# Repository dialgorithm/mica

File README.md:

# mica

**mica** is a compact wireless FPV drone built around an **XIAO ESP32-S3**, with a custom-designed flight controller and a custom 3D-printed frame. The project focuses on building a lightweight, self-contained drone platform with **ExpressLRS (ELRS)** control, custom electronics, and a mechanical design tailored specifically to the hardware.

it features:

- XIAO ESP32-S3 as the main flight controller
- Custom-designed flight controller PCB
- ExpressLRS (ELRS) for wireless control
- Custom 3D-printed frame

## design

mica is designed around keeping the electronics and mechanical structure compact while still leaving enough space for the components required for flight.

the flight controller is built around the XIAO ESP32-S3, with the supporting electronics integrated onto a custom PCB. the frame was designed specifically around the PCB and drone hardware rather than using an off-the-shelf frame.

the 3d-printed structure keeps the drone lightweight while providing mounting points for the electronics and other components. the overall layout is kept symmetrical to help maintain the center of gravity and make the drone predictable during flight.

## Schematics + PCB

Designed using KiCad.

| Schematic                          | PCB                    |
| ---------------------------------- | ---------------------- |
|  |  |

## CAD

final 3d mockup of the drone frame.

|                                   |                                     |
| --------------------------------- | ----------------------------------- |
|  |  |

the frame is 3d printable and was designed specifically around mica's electronics and component layout.

## BOM

the complete bill of materials is available in [`bom.csv`](bom.csv).

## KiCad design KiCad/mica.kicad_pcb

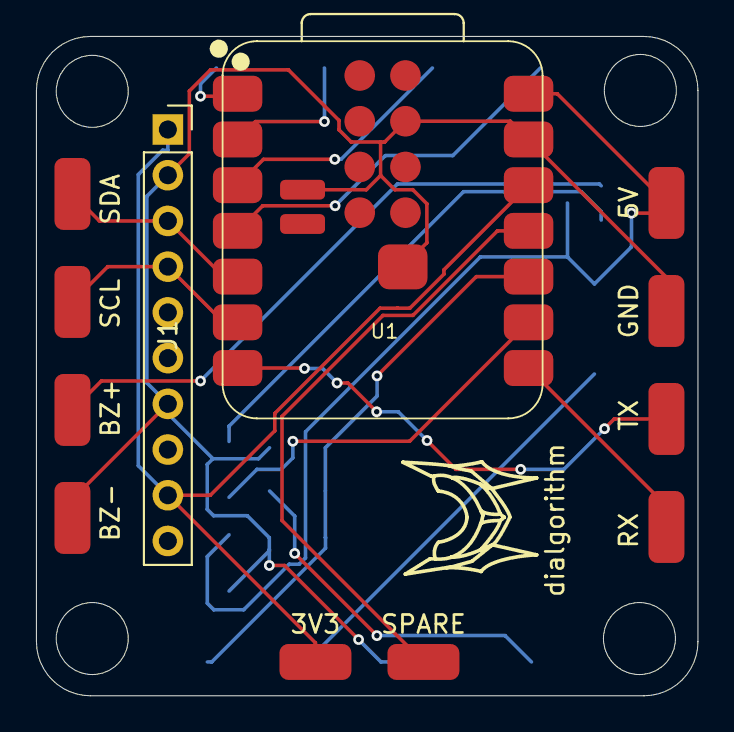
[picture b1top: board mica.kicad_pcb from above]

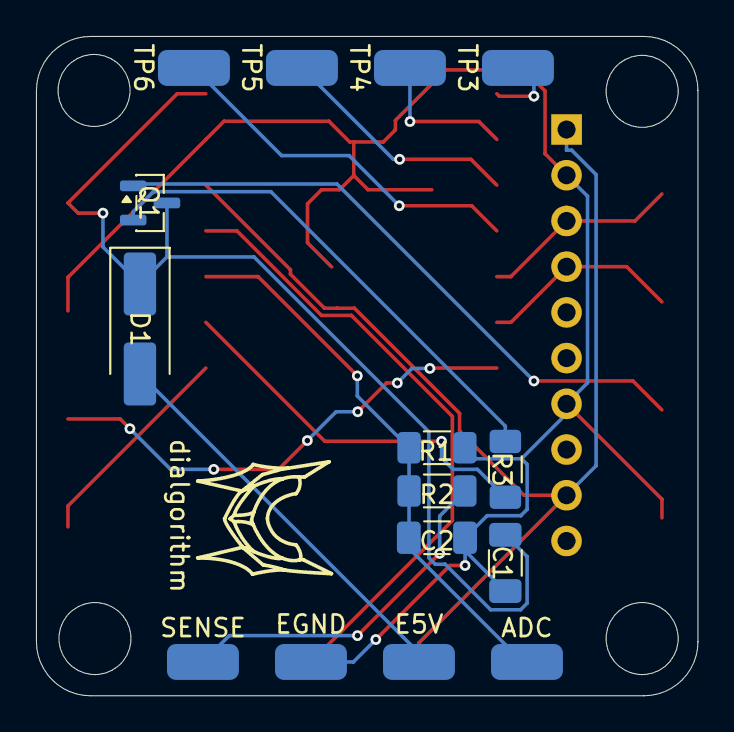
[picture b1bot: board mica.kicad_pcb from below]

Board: 2 copper layers, 36.8 x 36.6 mm, 29 parts (16 on the bottom side), 18 nets.

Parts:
3V3: 3V3; SolderWirePad_1x01_SMD_2x4mm
5V: ELRS_5V; SolderWirePad_1x01_SMD_2x4mm
ADC: VBAT_ADC; SolderWirePad_1x01_SMD_2x4mm
BZ+: BZ1+; SolderWirePad_1x01_SMD_2x4mm
BZ-: BZ1-; SolderWirePad_1x01_SMD_2x4mm
C1, C2: 100nF; C_1206_3216Metric_Pad1.33x1.80mm_HandSolder
D1: 1N5819; D_SMA_Handsoldering
E5V: ESC_5V; SolderWirePad_1x01_SMD_2x4mm
EGND: ESC_GND; SolderWirePad_1x01_SMD_2x4mm
GND: ELRS_GND; SolderWirePad_1x01_SMD_2x4mm
J1: J_IMU; PinSocket_1x10_P2.54mm_Vertical
Q1: 2N3906; SOT-23
R1: 3.3k; R_1206_3216Metric_Pad1.30x1.75mm_HandSolder
R2: 22k; R_1206_3216Metric_Pad1.30x1.75mm_HandSolder
R3: 2.2k; R_1206_3216Metric_Pad1.30x1.75mm_HandSolder
RX: ELRS_RX; SolderWirePad_1x01_SMD_2x4mm
SCL: I2C_SCL; SolderWirePad_1x01_SMD_2x4mm
SDA: I2C_SDA; SolderWirePad_1x01_SMD_2x4mm
SENSE: VBAT_SENSE; SolderWirePad_1x01_SMD_2x4mm
SPARE: Spare; SolderWirePad_1x01_SMD_2x4mm
TP3: ESC_M1; SolderWirePad_1x01_SMD_2x4mm
TP4: ESC_M2; SolderWirePad_1x01_SMD_2x4mm
TP5: ESC_M3; SolderWirePad_1x01_SMD_2x4mm
TP6: ESC_M4; SolderWirePad_1x01_SMD_2x4mm
TX: ELRS_TX; SolderWirePad_1x01_SMD_2x4mm
U1: XIAO-ESP32-S3-SMD
dialgorithm: dialgorithm
dialgorithm#2: dialgorithm

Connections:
BUZZER: R3.2, U1.9 (D8)
BZ1+: BZ+.1 (1_1), Q1.1 (C)
BZ1-: BZ-.1 (1_1), C1.2, C2.2, EGND.1 (1_1), GND.1 (1_1), J1.2, J1.7, R1.2, U1.13 (GND), U1.18 (GND), U1.24 (GND), U1.25 (PAD)
ELRS_5V: 5V.1 (1_1), C1.1, D1.1 (K), Q1.3 (E), U1.14 (VBUS)
ELRS_RX: RX.1 (1_1), U1.8 (D7)
ELRS_TX: TX.1 (1_1), U1.7 (D6)
I2C_SCL: J1.4, SCL.1 (1_1), U1.6 (D5)
I2C_SDA: J1.3, SDA.1 (1_1), U1.5 (D4)
IMU_NCS: 3V3.1 (1_1), J1.1, J1.9, U1.12 (3V3_OUT)
unnamed: D1.2 (A), E5V.1 (1_1)
unnamed: Q1.2 (B), R3.1
Spare: SPARE.1 (1_1), U1.11 (D10)
TP_ESC_M1: TP3.1 (1_1), U1.1 (D0)
TP_ESC_M2: TP4.1 (1_1), U1.2 (D1)
TP_ESC_M3: TP5.1 (1_1), U1.3 (D2)
TP_ESC_M4: TP6.1 (1_1), U1.4 (D3)
TP_VBAT_SENSE: R2.2, SENSE.1 (1_1)
VBAT_ADC: ADC.1 (1_1), C2.1, R1.1, R2.1, U1.10 (D9)
